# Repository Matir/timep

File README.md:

# Test Interface for Multiple Embedded Protocols

This is an Open Source Hardware board based around the FTDI FT2232H chip to
provide breakouts, buffering, and level conversion for a number of common
embedded hardware interfaces.  At present, this includes:

* SPI
* I2C
* JTAG
* SWD
* UART

It's intended to be easy to use and work with open source software, including
tools like OpenOCD and Flashrom.

## Archived

**This will not be maintained in any way. This eventually served as a prototype
and inspiration for [Tigard](https://github.com/tigard-tools/tigard), which was
productionized by [@securelyfitz](https://github.com/securelyfitz).**

## Usage

### Hardware Hookup

The hardware has dedicated headers for a variety of electrical interfaces.
Connect the desired interface to you target.  The pinout for SPI, I2C and UART
are printed on the board, SWD follows the ARM SWD standard, and JTAG is the ARM
20 pin JTAG interface.  (Electrically, however, it should work with most any
processor supporting JTAG.)

You may only use one of the SPI, I2C, SWD, and JTAG interfaces at any given
time.  The UART is handled by dedicated pins in the FT2232H, so can be used
simultaneously with one of the other interfaces.

There are 3 switches on the board.  The mode switch selects how the reference
power (for the interface) and the target are connected:

* **Isolated**: The interface is powered by the on-board voltage regulators, and the
  target must be powered by its own power supplies.  The power rails are not
  connected to one another.  You will almost always want to use this mode.
* **Bridged**: The interface is powered by the on-board voltage regulators which
  will also supply power to the target.  **The target must not be separately
  powered.**  This mode is useful for e.g., programming SPI/I2C flash out of
  circuit, or powering very small circuits -- maximum stable load is around 200mA.
* **Target**: The interface is partially powered from the target.
  (Specifically, the reference voltage for the level shifters.)  In theory, this
  can be used for cases where the target voltage is not 5v, 3.3v, or 1.8v.  The
  target voltage must still remain under 5V!

Note that the *ground* of your computer is connected to the *ground* of your
target when you connect with this.  In almost all cases, this is not a problem,
but if both are powered via the wall ("mains"), there is a risk of noise due to
ground loops, etc.

The voltage switch allows you to select the I/O voltage used in `Isolated` or
`Bridged` mode.  It does nothing (well, except change an LED) in `Target` mode.
5V is supplied directly from the USB input, and there are onboard regulators
for 3.3v and 1.8v.

The remaining switch selects between JTAG/SPI and I2C/SWD.  I2C and SWD use a
bidirectional data line, so require special handling.

### Software

I've tested the board with `OpenOCD` for JTAG/SWD use and `flashrom` for SPI/I2C
flash.  I'm planning to make a demo target board with a handful of interfaces on
it and provide that here in the future.

With `OpenOCD`, use the configuration file in `configs`.  You will also need a
target configuration.  Time permitting, I will post a tutorial on the use of
TIMEP and OpenOCD to debug targets.

With `flashrom`:

```
flashrom -p ft2232_spi:type=2232H,port=B,divisor=4
```

Use of `port=B` is critical, port `A` is wired to the UART, so will not work as
you intend.  :)

### Protections

Some efforts have been made to protect against mistakes that will destroy your
hardware, but there is still some risk in using this if connected improperly.

Included protection in current revision:

* Current limiting resistors on I/O lines.
* 5v+ tolerant I/O.
* Warnings in the README.  :)

Shorting power to ground may damage the target, the TIMEP interface, or the USB
port on your computer (if running in 5V mode).  This is unlikely, but be careful
with your connections.

Using the wrong voltage may damage components not rated for that voltage.  Any
voltage up to 5v is tolerated on the interface board I/O pins, but beyond that
may result in damage.

Additional protection that could be considered:

* Polyfuses on power/ground rails to computer.
* Clamping diodes on USB lines.
* Clamping diodes on I/O lines.

These have not been added because I have been trying to keep BOM cost down to
get these in the hands of as many hardware hackers as possible.

## License

Copyright 2020 Google, LLC

Maintainer: David Tomaschik <david@systemoverlord.com>

Please see [CONTRIBUTORS.md](CONTRIBUTORS.md) for credit to all contributors.

Licensed under the Apache License, Version 2.0 (the "License");
you may not use this file except in compliance with the License.
You may obtain a copy of the License at

    https://www.apache.org/licenses/LICENSE-2.0

Unless required by applicable law or agreed to in writing, software
distributed under the License is distributed on an "AS IS" BASIS,
WITHOUT WARRANTIES OR CONDITIONS OF ANY KIND, either express or implied.
See the License for the specific language governing permissions and
limitations under the License.

This is not an officially supported Google product.

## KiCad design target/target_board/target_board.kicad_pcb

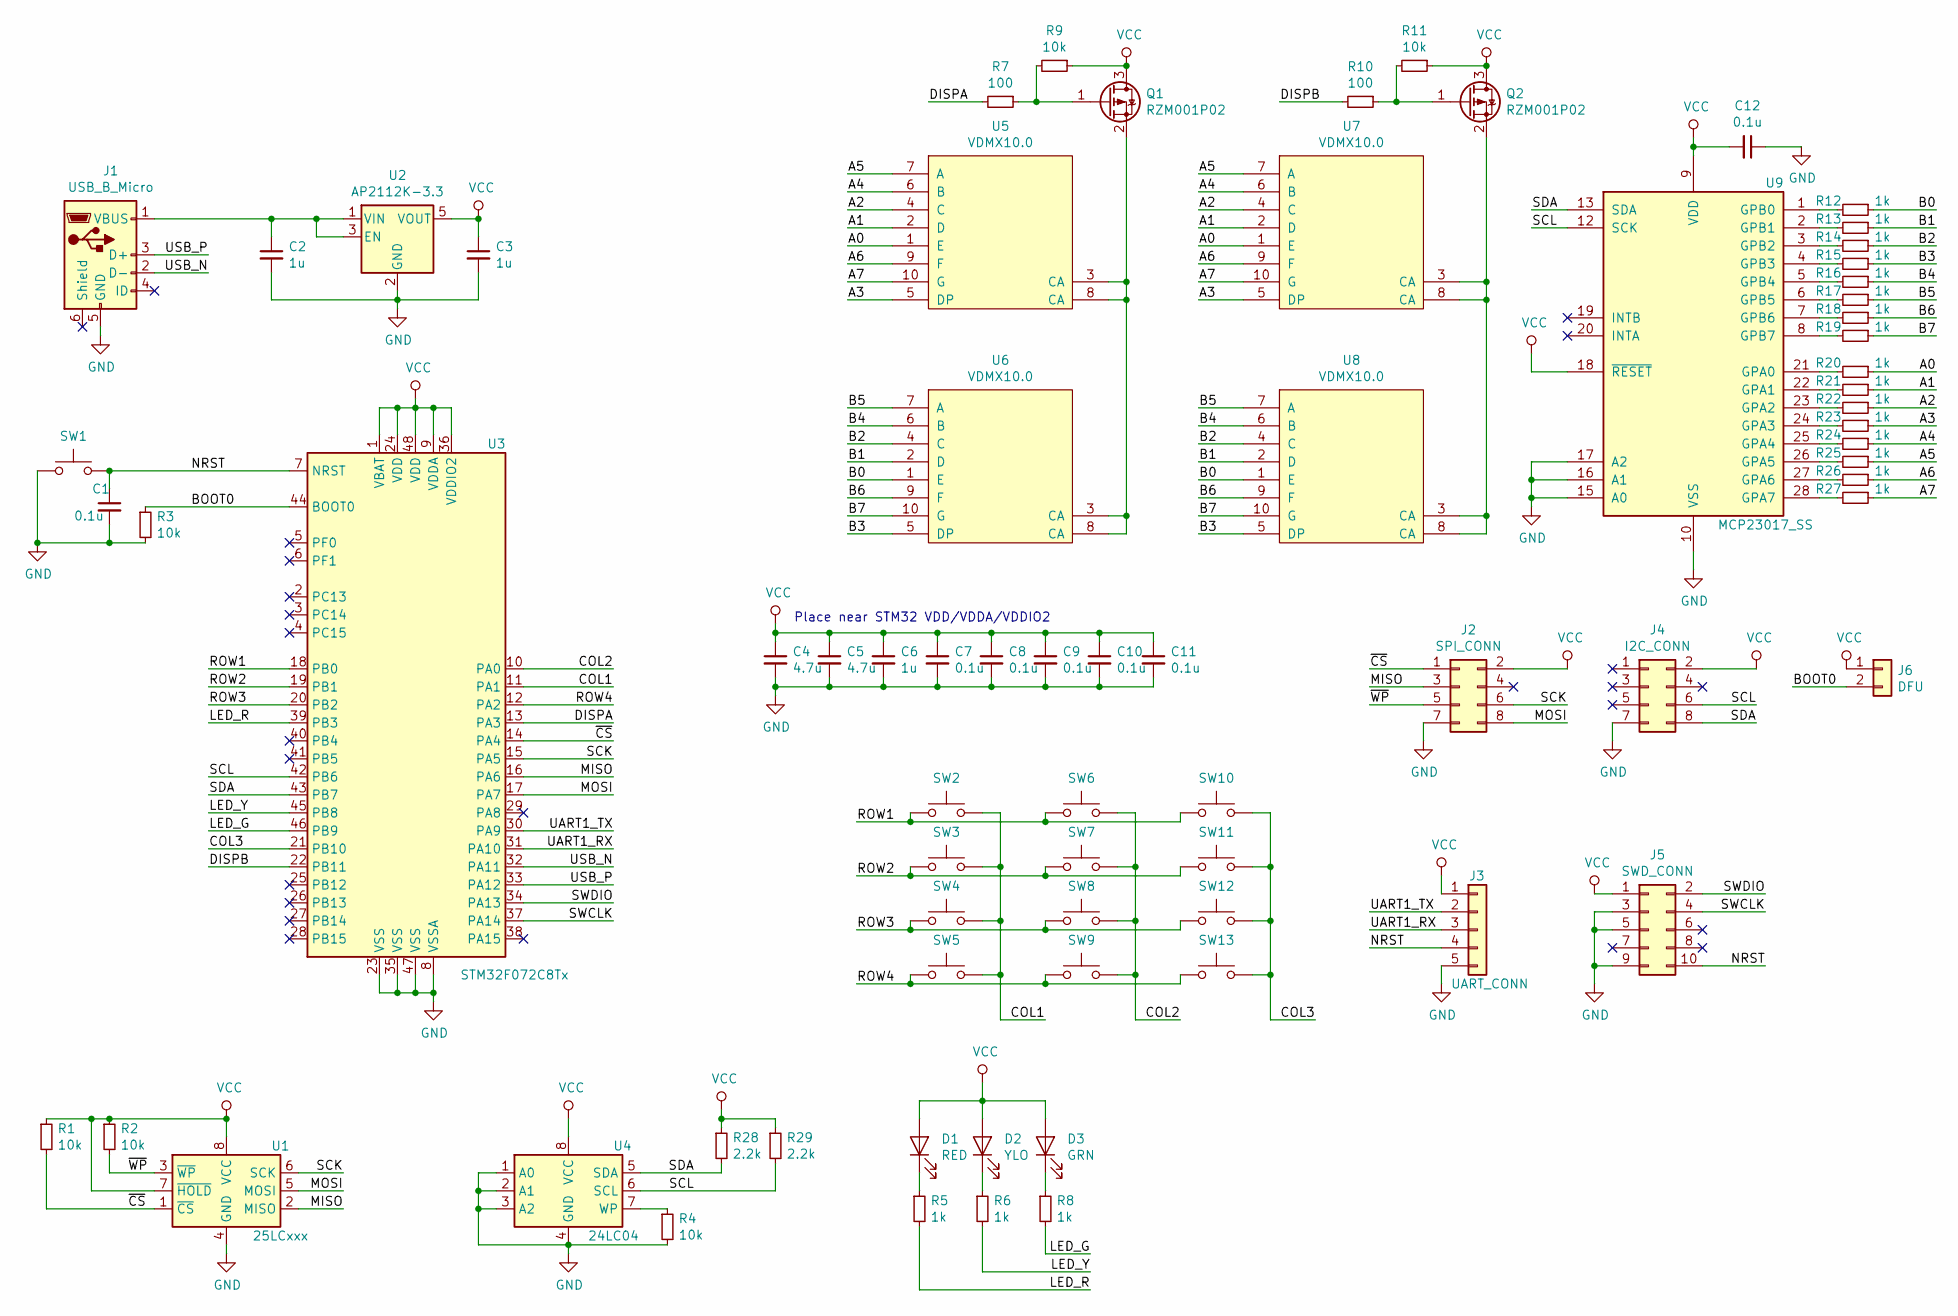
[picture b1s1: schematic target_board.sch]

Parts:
C1, C7, C8, C9, C10, C11, C12: 0.1u; C_0603_1608Metric
C2, C3, C6: 1u; C_0603_1608Metric
C4, C5: 4.7u; C_0603_1608Metric
D1: RED; LED_0603_1608Metric_Castellated
D2: YLO; LED_0603_1608Metric_Castellated
D3: GRN; LED_0603_1608Metric_Castellated
J1: USB_B_Micro; USB_Micro-B_Amphenol_10103594-0001LF_Horizontal
J2: SPI_CONN; PinHeader_2x04_P2.54mm_Vertical
J3: UART_CONN; PinHeader_1x05_P2.54mm_Vertical
J4: I2C_CONN; PinHeader_2x04_P2.54mm_Vertical
J5: SWD_CONN; PinHeader_2x05_P1.27mm_Vertical
J6: DFU; PinHeader_1x02_P2.54mm_Vertical
Q1, Q2: RZM001P02; SOT-723
R1, R2, R3, R4, R9, R11: 10k; R_0603_1608Metric
R5, R6, R8, R12, R13, R14, R15, R16, R17, R18, R19, R20, R21, R22, R23, R24, R25, R26, R27: 1k; R_0603_1608Metric
R7, R10: 100; R_0603_1608Metric
R28, R29: 2.2k; R_0603_1608Metric
SW1, SW2, SW3, SW4, SW5, SW6, SW7, SW8, SW9, SW10, SW11, SW12, SW13: SW_Push; SW_SPST_PTS645
U1: 25LCxxx; SOIC-8_3.9x4.9mm_P1.27mm
U2: AP2112K-3.3; SOT-23-5
U3: STM32F072C8Tx; LQFP-48_7x7mm_P0.5mm
U4: 24LC04; SOIC-8_3.9x4.9mm_P1.27mm
U5, U6, U7, U8: VDMX10.0
U9: MCP23017_SS; SSOP-28_5.3x10.2mm_P0.65mm

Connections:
/A0: R20.1, U5.1 (E), U7.1 (E)
/A1: R21.1, U5.2 (D), U7.2 (D)
/A2: R22.1, U5.4 (C), U7.4 (C)
/A3: R23.1, U5.5 (DP), U7.5 (DP)
/A4: R24.1, U5.6 (B), U7.6 (B)
/A5: R25.1, U5.7 (A), U7.7 (A)
/A6: R26.1, U5.9 (F), U7.9 (F)
/A7: R27.1, U5.10 (G), U7.10 (G)
/B0: R12.1, U6.1 (E), U8.1 (E)
/B1: R13.1, U6.2 (D), U8.2 (D)
/B2: R14.1, U6.4 (C), U8.4 (C)
/B3: R15.1, U6.5 (DP), U8.5 (DP)
/B4: R16.1, U6.6 (B), U8.6 (B)
/B5: R17.1, U6.7 (A), U8.7 (A)
/B6: R18.1, U6.9 (F), U8.9 (F)
/B7: R19.1, U6.10 (G), U8.10 (G)
/BOOT0: J6.2, R3.1, U3.44 (BOOT0)
/COL1: SW2.2, SW3.2, SW4.2, SW5.2, U3.11 (PA1)
/COL2: SW6.2, SW7.2, SW8.2, SW9.2, U3.10 (PA0)
/COL3: SW10.2, SW11.2, SW12.2, SW13.2, U3.21 (PB10)
/DISPA: R7.2, U3.13 (PA3)
/DISPB: R10.2, U3.22 (PB11)
/LED_G: R8.2, U3.46 (PB9)
/LED_R: R5.2, U3.39 (PB3)
/LED_Y: R6.2, U3.45 (PB8)
/MISO: J2.3, U1.2 (MISO), U3.16 (PA6)
/MOSI: J2.8, U1.5 (MOSI), U3.17 (PA7)
/NRST: C1.1, J3.4, J5.10, SW1.2, U3.7 (NRST)
/ROW1: SW2.1, SW6.1, SW10.1, U3.18 (PB0)
/ROW2: SW3.1, SW7.1, SW11.1, U3.19 (PB1)
/ROW3: SW4.1, SW8.1, SW12.1, U3.20 (PB2)
/ROW4: SW5.1, SW9.1, SW13.1, U3.12 (PA2)
/SCK: J2.6, U1.6 (SCK), U3.15 (PA5)
/SCL: J4.6, R29.2, U3.42 (PB6), U4.6 (SCL), U9.12 (SCK)
/SDA: J4.8, R28.2, U3.43 (PB7), U4.5 (SDA), U9.13 (SDA)
/SWCLK: J5.4, U3.37 (PA14)
/SWDIO: J5.2, U3.34 (PA13)
/UART1_RX: J3.3, U3.31 (PA10)
/UART1_TX: J3.2, U3.30 (PA9)
/USB_N: J1.2 (D-), U3.32 (PA11)
/USB_P: J1.3 (D+), U3.33 (PA12)
/~CS: J2.1, R1.2, U1.1 (~CS), U3.14 (PA4)
/~WP: J2.5, R2.2, U1.3 (~WP)
GND: C1.2, C2.2, C3.2, C4.2, C5.2, C6.2, C7.2, C8.2, C9.2, C10.2, C11.2, C12.1, J1.5 (GND), J2.7, J3.5, J4.7, J5.3, J5.5, J5.9, R3.2, R4.2, SW1.1, U1.4 (GND), U2.2 (GND), U3.8 (VSSA), U3.23 (VSS), U3.35 (VSS), U3.47 (VSS), U4.1 (A0), U4.2 (A1), U4.3 (A2), U4.4 (GND), U9.10 (VSS), U9.15 (A0), U9.16 (A1), U9.17 (A2)
unnamed: C2.1, J1.1 (VBUS), U2.1 (VIN), U2.3 (EN)
unnamed: D1.1 (K), R5.1
unnamed: D2.1 (K), R6.1
unnamed: D3.1 (K), R8.1
unnamed: Q1.1 (G), R7.1, R9.2
unnamed: Q1.2 (S), U5.3 (CA), U5.8 (CA), U6.3 (CA), U6.8 (CA)
unnamed: Q2.1 (G), R10.1, R11.2
unnamed: Q2.2 (S), U7.3 (CA), U7.8 (CA), U8.3 (CA), U8.8 (CA)
unnamed: R4.1, U4.7 (WP)
unnamed: R12.2, U9.1 (GPB0)
unnamed: R13.2, U9.2 (GPB1)
unnamed: R14.2, U9.3 (GPB2)
unnamed: R15.2, U9.4 (GPB3)
unnamed: R16.2, U9.5 (GPB4)
unnamed: R17.2, U9.6 (GPB5)
unnamed: R18.2, U9.7 (GPB6)
unnamed: R19.2, U9.8 (GPB7)
unnamed: R20.2, U9.21 (GPA0)
unnamed: R21.2, U9.22 (GPA1)
unnamed: R22.2, U9.23 (GPA2)
unnamed: R23.2, U9.24 (GPA3)
unnamed: R24.2, U9.25 (GPA4)
unnamed: R25.2, U9.26 (GPA5)
unnamed: R26.2, U9.27 (GPA6)
unnamed: R27.2, U9.28 (GPA7)
VCC: C3.1, C4.1, C5.1, C6.1, C7.1, C8.1, C9.1, C10.1, C11.1, C12.2, D1.2 (A), D2.2 (A), D3.2 (A), J2.2, J3.1, J4.2, J5.1, J6.1, Q1.3 (D), Q2.3 (D), R1.1, R2.1, R9.1, R11.1, R28.1, R29.1, U1.7 (~HOLD), U1.8 (VCC), U2.5 (VOUT), U3.1 (VBAT), U3.9 (VDDA), U3.24 (VDD), U3.36 (VDDIO2), U3.48 (VDD), U4.8 (VCC), U9.9 (VDD), U9.18 (~RESET~)

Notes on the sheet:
Place near STM32 VDD/VDDA/VDDIO2

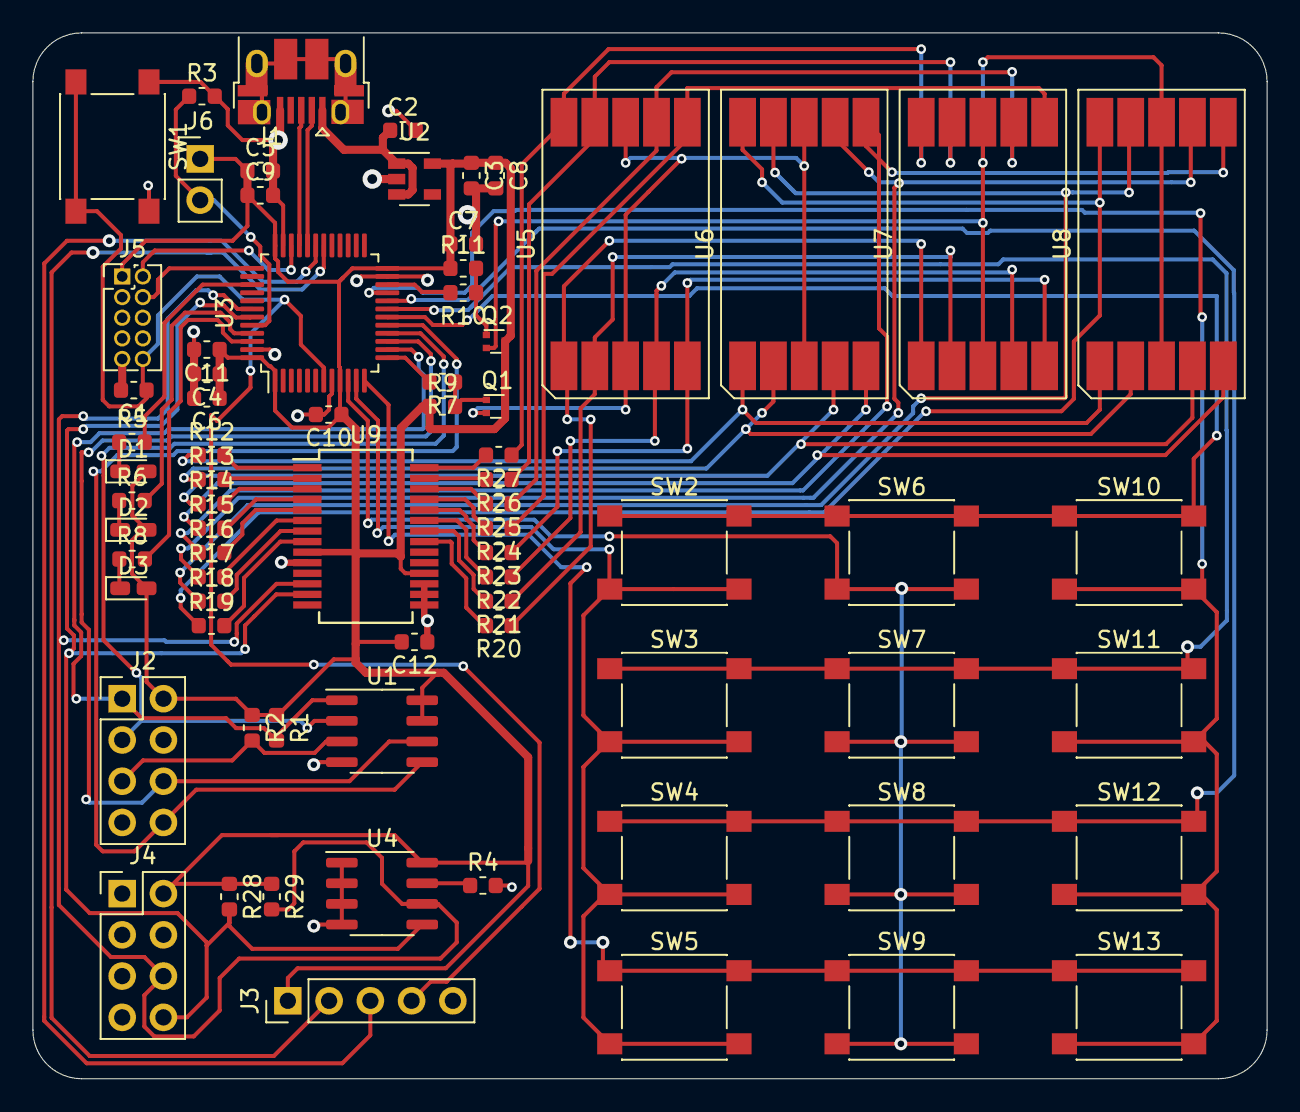
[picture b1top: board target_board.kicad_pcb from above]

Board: 2 copper layers, 76.0 x 64.4 mm, 74 parts (0 on the bottom side), 70 nets.

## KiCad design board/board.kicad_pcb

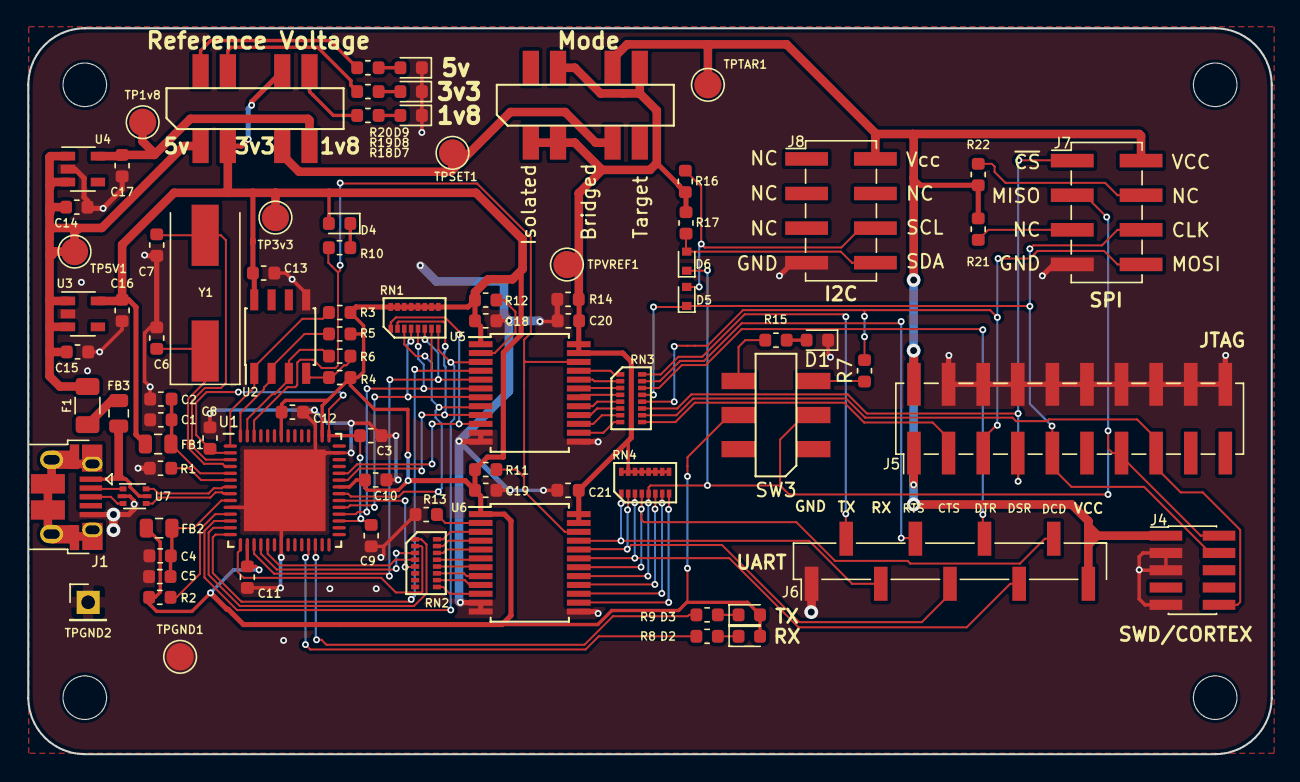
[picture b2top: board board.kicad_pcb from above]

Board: 2 copper layers, 91.3 x 53.3 mm, 89 parts (0 on the bottom side), 90 nets.

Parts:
C1, C4: 2.2u; C_0603_1608Metric
C2, C5, C8, C9, C10, C11, C12, C13, C18, C19, C20, C21: 0.1u; C_0603_1608Metric
C3, C14, C15, C16, C17: 3.3u; C_0603_1608Metric
C6, C7: 27pf; C_0603_1608Metric
D1, D2, D3, D4: LED; LED_0603_1608Metric
D5, D6: RB751S40; D_SOD-523
D7: 1v8; LED_0603_1608Metric
D8: 3v3; LED_0603_1608Metric
D9: 5v; LED_0603_1608Metric
F1: 500mA; Fuse_1206_3216Metric
FB1, FB2, FB3: 100; L_0805_2012Metric
H1, H2, H3, H4: MountingHole; MountingHole_3.2mm_M3
J1: USB_B_Micro; USB_Micro-B_Amphenol_10103594-0001LF_Horizontal
J4: SWD_CONN; PinHeader_2x05_P1.27mm_Vertical_SMD
J5: JTAG_CONN; PinHeader_2x10_P2.54mm_Vertical_SMD
J6: UART_Conn; PinHeader_1x09_P2.54mm_Vertical_SMD_Pin1Left
J7: SPI_CONN; PinHeader_2x04_P2.54mm_Vertical_SMD
J8: I2C_CONN; PinHeader_2x04_P2.54mm_Vertical_SMD
R1: 12k, 1%; R_0603_1608Metric
R2, R3, R4, R6, R11, R12, R13, R21, R22: 10k; R_0603_1608Metric
R5, R16, R17: 2.2k; R_0603_1608Metric
R7: 330; R_0603_1608Metric
R8, R9, R10, R15, R18, R19, R20: 1k; R_0603_1608Metric
R14: 1M; R_0603_1608Metric
RN1, RN4: 100k; EXB2HV
RN2, RN3: 100; EXB2HV
SW1, SW2: SW_DP3T; JS203011SCQN
SW3: SW_DPDT_x2; JS202011SCQN
TP1v8, TP3v3: TestPoint; TestPoint_Pad_D2.0mm
TP5V1: TP5V; TestPoint_Pad_D2.0mm
TPGND1: TestPoint; TestPoint_Pad_D2.0mm
TPGND2: TestPoint; PinHeader_1x01_P2.54mm_Vertical
TPSET1: TestPoint; TestPoint_Pad_D2.0mm
TPTAR1: TestPoint; TestPoint_Pad_D2.0mm
TPVREF1: TestPoint; TestPoint_Pad_D2.0mm
U1: FT2232H-56; FT2232H-56Q
U2: 93LC46B; SOIC-8_3.9x4.9mm_P1.27mm
U3: AP2112K-3.3; SOT-23-5
U4: AP2112K-1.8; SOT-23-5
U5, U6: SN74LVC8T245; SSOP-24_5.3x8.2mm_P0.65mm
U7: USBLC6; SOT-666
Y1: 12.000MHz; Crystal_SMD_HC49-SD

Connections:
+1V8: C17.1, SW1.4, TP1v8.1, U4.5
+3V3: C10.1, C11.1, C12.1, C13.1, C16.1, C18.1, C19.1, D2.2, D3.2, D4.2, FB1.1, FB2.1, R2.2, R3.1, R4.1, R6.1, R11.1, R12.2, RN1.9, RN1.10, RN1.11, RN1.12, RN1.13, RN1.14, RN1.15, RN1.16, SW1.2, SW1.7, SW3.5, TP3v3.1, U1.16, U1.36, U1.44, U1.50, U2.8, U3.5, U5.1, U6.1
+5V: C14.1, C15.1, F1.1, SW1.1, TP5V1.1, U3.1, U3.3, U4.1, U4.3
/AD0: RN1.8, U1.12, U5.3
/AD1: RN2.1, U1.13
/AD2: RN1.7, U1.14, U5.4
/AD3: RN2.2, U1.15
/AD4: RN1.6, U1.17, U5.5
/AD5: RN2.3, U1.18
/AD6: RN2.4, U1.19
/BD0: RN1.5, U1.32, U5.6
/BD1: RN1.4, U1.33, U5.7
/BD2: RN2.5, U1.34
/BD3: RN1.3, U1.35, U5.8
/BD4: RN1.2, U1.37, U5.9
/BD5: RN1.1, U1.38, U5.10
/CLK: D5.1, J4.4, J5.9, J7.6, RN3.13
/CS: J5.7, J7.1, RN3.11
/DI: D6.1, J4.2, J5.13, J7.3, RN4.5, SW3.2, U6.17
/DO: J5.5, J7.8, R7.2, RN3.12
/FT2232 Module/EECLK: R6.2, U1.56, U2.2
/FT2232 Module/EECS: R3.2, U1.1, U2.1
/FT2232 Module/EEDATA: R5.1, U1.55, U2.3
/FT2232 Module/OSCI: C7.1, U1.3, Y1.2
/FT2232 Module/OSCO: C6.1, U1.4, Y1.1
/FT2232 Module/VPHY: C1.1, C2.1, FB1.2, U1.5
/FT2232 Module/VPLL: C4.1, C5.1, FB2.2, U1.9
/FT2232 Module/VREG: C3.1, C8.1, C9.1, U1.2, U1.31, U1.43
/Power Regulators/Vset: SW1.3, SW2.3, TPSET1.1
/RXLED: R8.2, U1.25
/SCL: D5.2, J8.6, R16.2
/SDA: D6.2, J8.8, R17.2
/TXLED: R9.2, U1.26
/UART_RX: J6.3, RN4.1, U6.21
/UART_TX: J6.2, RN3.16
/USB_N: U1.7, U7.6
/USB_P: U1.8, U7.4
/VBUS: FB3.2, J1.1, U7.5
/VREF: C20.1, C21.1, R14.1, R16.1, R17.1, RN4.9, RN4.10, RN4.11, RN4.12, RN4.13, RN4.14, RN4.15, RN4.16, SW2.1, SW2.2, SW2.6, SW2.8, TPVREF1.1, U5.23, U5.24, U6.23, U6.24
/VTARGET: J4.1, J5.1, J5.2, J6.9, J7.2, J8.2, R21.2, R22.1, SW2.7, TPTAR1.1
/~ENABLE: R10.2, R11.2, U1.54, U5.22, U6.22
/~SRST: J4.10, J5.15, RN3.10
/~TRST: J5.3, RN3.9
/~UART_CTS: J6.5, RN4.2, U6.20
/~UART_DCD: J6.8, RN4.4, U6.18
/~UART_DSR: J6.7, RN4.3, U6.19
/~UART_DTR: J6.6, RN3.14
/~UART_RTS: J6.4, RN3.15
GND: C1.2, C2.2, C3.2, C4.2, C5.2, C6.2, C7.2, C8.2, C9.2, C10.2, C11.2, C12.2, C13.2, C14.2, C15.2, C16.2, C17.2, C18.2, C19.2, C20.2, C21.2, D1.1, D7.1, D8.1, D9.1, J1.5, J4.3, J4.5, J4.9, J5.4, J5.6, J5.8, J5.10, J5.12, J5.14, J5.16, J5.18, J5.20, J6.1, J7.7, J8.7, R1.2, R13.2, R14.2, TPGND1.1, TPGND2.1, U1.10, U1.21, U1.41, U1.45, U2.5, U3.2, U4.2, U5.11, U5.12, U5.13, U6.11, U6.12, U6.13, U7.2
unnamed: D1.2, R15.2
unnamed: D2.1, R8.1
unnamed: D3.1, R9.1
unnamed: D4.1, R10.1
unnamed: D7.2, R18.2
unnamed: D8.2, R19.2
unnamed: D9.2, R20.2
unnamed: F1.2, FB3.1
unnamed: J1.2, U7.1
unnamed: J1.3, U7.3
unnamed: J7.4, R22.2
unnamed: J7.5, R21.1
unnamed: R1.1, U1.6
unnamed: R2.1, U1.11
unnamed: R4.2, R5.2, U2.4
unnamed: R7.1, SW3.3
unnamed: R12.1, U5.2
unnamed: R13.1, U6.2
unnamed: R15.1, SW3.6
unnamed: R18.1, SW1.8
unnamed: R19.1, SW1.6
unnamed: R20.1, SW1.5
unnamed: RN2.9, U6.10
unnamed: RN2.10, U6.9
unnamed: RN2.11, U6.8
unnamed: RN2.12, U6.7
unnamed: RN2.13, U6.6
unnamed: RN2.14, U6.5
unnamed: RN2.15, U6.4
unnamed: RN2.16, U6.3
unnamed: RN3.1, U5.21
unnamed: RN3.2, U5.20
unnamed: RN3.3, U5.19
unnamed: RN3.4, U5.18
unnamed: RN3.5, U5.17
unnamed: RN3.6, U5.16
unnamed: RN3.7, U5.15
unnamed: RN3.8, U5.14
unnamed: RN4.6, U6.16
unnamed: RN4.7, U6.15
unnamed: RN4.8, U6.14

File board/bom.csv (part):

Reference, Value, Footprint, Datasheet, Digikey, P/N, Comment
"J1","USB_B_Micro","Connector_USB:USB_Micro-B_Amphenol_10103594-0001LF_Horizontal","~","609-4050-1-ND","10103594",""
"FB3","100","Inductor_SMD:L_0805_2012Metric","~","445-1567-1-ND","MPZ2012S101AT000",""
"D2","LED","LED_SMD:LED_0603_1608Metric","~","732-4979-1-ND","150060SS75000","Substitution Okay"
"D3","LED","LED_SMD:LED_0603_1608Metric","~","732-4979-1-ND","150060SS75000","Substitution Okay"
"R8","1k","Resistor_SMD:R_0603_1608Metric","~","RMCF0603JT1K00CT-ND","RMCF0603JT1K00","Substitution Okay"
"R9","1k","Resistor_SMD:R_0603_1608Metric","~","RMCF0603JT1K00CT-ND","RMCF0603JT1K00","Substitution Okay"
"D4","LED","LED_SMD:LED_0603_1608Metric","~","732-4979-1-ND","150060SS75000","Substitution Okay"
"R10","1k","Resistor_SMD:R_0603_1608Metric","~","RMCF0603JT1K00CT-ND","RMCF0603JT1K00","Substitution Okay"
"U5","SN74LVC8T245","Package_SO:SSOP-24_5.3x8.2mm_P0.65mm","","296-21065-1-ND","SN74LVC8T245DBR",""
"U6","SN74LVC8T245","Package_SO:SSOP-24_5.3x8.2mm_P0.65mm","","296-21065-1-ND","SN74LVC8T245DBR",""
"R11","10k","Resistor_SMD:R_0603_1608Metric","~","RMCF0603JT10K0CT-ND","RMCF0603JT10K0","Substitution Okay"
"C18","0.1u","Capacitor_SMD:C_0603_1608Metric","~","1276-1857-1-ND","CL10A104KA8NNNC","Substitution Okay"
"C19","0.1u","Capacitor_SMD:C_0603_1608Metric","~","1276-1857-1-ND","CL10A104KA8NNNC","Substitution Okay"
"C20","0.1u","Capacitor_SMD:C_0603_1608Metric","~","1276-1857-1-ND","CL10A104KA8NNNC","Substitution Okay"
"C21","0.1u","Capacitor_SMD:C_0603_1608Metric","~","1276-1857-1-ND","CL10A104KA8NNNC","Substitution Okay"
"R12","10k","Resistor_SMD:R_0603_1608Metric","~","RMCF0603JT10K0CT-ND","RMCF0603JT10K0","Substitution Okay"
"R13","10k","Resistor_SMD:R_0603_1608Metric","~","RMCF0603JT10K0CT-ND","RMCF0603JT10K0","Substitution Okay"
"R14","1M","Resistor_SMD:R_0603_1608Metric","~","RMCF0603JT1M00CT-ND","RMCF0603JT1M00","Substitution Okay"
"RN1","100k","Matir_Parts:EXB2HV","~","Y1104CT-ND","EXB-2HV104JV",""
"RN2","100","Matir_Parts:EXB2HV","~","Y1331CT-ND","EXB-2HV331JV",""
"RN4","100k","Matir_Parts:EXB2HV","~","Y1104CT-ND","EXB-2HV104JV",""
"RN3","100","Matir_Parts:EXB2HV","~","Y1331CT-ND","EXB-2HV331JV",""
"J6","UART_Conn","Connector_PinHeader_2.54mm:PinHeader_1x09_P2.54mm_Vertical_SMD_Pin1Left","~","TSM-109-01-L-SV-P-ND","TSM-109-01-L-SV-P",""
"J5","JTAG_CONN","Connector_PinHeader_2.54mm:PinHeader_2x10_P2.54mm_Vertical_SMD","~","609-6477-1-ND","95278-801A20LF",""
"J4","SWD_CONN","Connector_PinHeader_1.27mm:PinHeader_2x05_P1.27mm_Vertical_SMD","~","609-6118-1-ND","20021121-00010C1L",""
"J7","SPI_CONN","Connector_PinHeader_2.54mm:PinHeader_2x04_P2.54mm_Vertical_SMD","~","609-5811-1-ND","95278-101A08LF",""
"J8","I2C_CONN","Connector_PinHeader_2.54mm:PinHeader_2x04_P2.54mm_Vertical_SMD","~","609-5811-1-ND","95278-101A08LF",""
"R16","2.2k","Resistor_SMD:R_0603_1608Metric","~","RMCF0603JT2K20CT-ND","RMCF0603JT2K20","Substitution Okay"
"R17","2.2k","Resistor_SMD:R_0603_1608Metric","~","RMCF0603JT2K20CT-ND","RMCF0603JT2K20","Substitution Okay"
"D5","RB751S40","Diode_SMD:D_SOD-523","~","RB751S40T1GOSCT-ND","RB751S40T1G",""
"D6","RB751S40","Diode_SMD:D_SOD-523","~","RB751S40T1GOSCT-ND","RB751S40T1G",""
"H4","MountingHole","MountingHole:MountingHole_3.2mm_M3","~"
"H2","MountingHole","MountingHole:MountingHole_3.2mm_M3","~"
"H1","MountingHole","MountingHole:MountingHole_3.2mm_M3","~"
"H3","MountingHole","MountingHole:MountingHole_3.2mm_M3","~"
"SW3","SW_DPDT_x2","Matir_Parts:JS202011SCQN","","401-2002-1-ND","JS202011SCQN",""
"R7","330","Resistor_SMD:R_0603_1608Metric","~","RMCF0603JT330RCT-ND","RMCF0603JT330R","Substitution Okay"
"R15","1k","Resistor_SMD:R_0603_1608Metric","~","RMCF0603JT1K00CT-ND","RMCF0603JT1K00","Substitution Okay"
"D1","LED","LED_SMD:LED_0603_1608Metric","~","732-4979-1-ND","150060SS75000","Substitution Okay"
"R22","10k","Resistor_SMD:R_0603_1608Metric","~","RMCF0603JT10K0CT-ND","RMCF0603JT10K0","Substitution Okay"
"R21","10k","Resistor_SMD:R_0603_1608Metric","~","RMCF0603JT10K0CT-ND","RMCF0603JT10K0","Substitution Okay"
"F1","500mA","Fuse:Fuse_1206_3216Metric","~","NANOSMDC050F/13.2-2CT-ND","NANOSMDC050F/13.2-2",""
"U7","USBLC6","Package_TO_SOT_SMD:SOT-666","","497-5026-1-ND","USBLC6-2P6",""
"U1","FT2232H-56","Matir_Parts:FT2232H-56Q","","768-1276-ND","FT2232H-56Q-TRAY",""
"C3","3.3u","Capacitor_SMD:C_0603_1608Metric","~","1276-1892-1-ND","CL10A335KP8NNNC","Substitution Okay"
"R1","12k, 1%","Resistor_SMD:R_0603_1608Metric","~","RMCF0603FT12K0CT-ND","RMCF0603FT12K0",""
"FB2","100","Inductor_SMD:L_0805_2012Metric","~","445-1567-1-ND","MPZ2012S101AT000",""
"FB1","100","Inductor_SMD:L_0805_2012Metric","~","445-1567-1-ND","MPZ2012S101AT000",""
"C4","2.2u","Capacitor_SMD:C_0603_1608Metric","~","1276-1183-1-ND","CL10A225KQ8NNNC","Substitution Okay"
"C2","0.1u","Capacitor_SMD:C_0603_1608Metric","~","1276-1857-1-ND","CL10A104KA8NNNC","Substitution Okay"
"C5","0.1u","Capacitor_SMD:C_0603_1608Metric","~","1276-1857-1-ND","CL10A104KA8NNNC","Substitution Okay"
"C1","2.2u","Capacitor_SMD:C_0603_1608Metric","~","1276-1183-1-ND","CL10A225KQ8NNNC","Substitution Okay"
"C8","0.1u","Capacitor_SMD:C_0603_1608Metric","~","1276-1857-1-ND","CL10A104KA8NNNC","Substitution Okay"
"C9","0.1u","Capacitor_SMD:C_0603_1608Metric","~","1276-1857-1-ND","CL10A104KA8NNNC","Substitution Okay"
"C10","0.1u","Capacitor_SMD:C_0603_1608Metric","~","1276-1857-1-ND","CL10A104KA8NNNC","Substitution Okay"
"C11","0.1u","Capacitor_SMD:C_0603_1608Metric","~","1276-1857-1-ND","CL10A104KA8NNNC","Substitution Okay"
"C12","0.1u","Capacitor_SMD:C_0603_1608Metric","~","1276-1857-1-ND","CL10A104KA8NNNC","Substitution Okay"
"R2","10k","Resistor_SMD:R_0603_1608Metric","~","RMCF0603JT10K0CT-ND","RMCF0603JT10K0","Substitution Okay"
"Y1","12.000MHz","Crystal:Crystal_SMD_HC49-SD","~","535-15006-1-ND","ABLS-12.000MHZ-20-B-3-H-T",""
"C7","27pf","Capacitor_SMD:C_0603_1608Metric","~","311-1063-1-ND","CC0603JRNPO9BN270",""
"C6","27pf","Capacitor_SMD:C_0603_1608Metric","~","311-1063-1-ND","CC0603JRNPO9BN270",""
"U2","93LC46B","Package_SO:SOIC-8_3.9x4.9mm_P1.27mm","http://ww1.microchip.com/downloads/en/DeviceDoc/20001749K.pdf","93LC46BT-I/SNCT-ND","93LC46BT-I/SN",""
"C13","0.1u","Capacitor_SMD:C_0603_1608Metric","~","1276-1857-1-ND","CL10A104KA8NNNC","Substitution Okay"
"R4","10k","Resistor_SMD:R_0603_1608Metric","~","RMCF0603JT10K0CT-ND","RMCF0603JT10K0","Substitution Okay"
"R6","10k","Resistor_SMD:R_0603_1608Metric","~","RMCF0603JT10K0CT-ND","RMCF0603JT10K0","Substitution Okay"
"R3","10k","Resistor_SMD:R_0603_1608Metric","~","RMCF0603JT10K0CT-ND","RMCF0603JT10K0","Substitution Okay"
"R5","2.2k","Resistor_SMD:R_0603_1608Metric","~","RMCF0603JT2K20CT-ND","RMCF0603JT2K20","Substitution Okay"
"C16","3.3u","Capacitor_SMD:C_0603_1608Metric","~","1276-1892-1-ND","CL10A335KP8NNNC","Substitution Okay"
"C14","3.3u","Capacitor_SMD:C_0603_1608Metric","~","1276-1892-1-ND","CL10A335KP8NNNC","Substitution Okay"
"C15","3.3u","Capacitor_SMD:C_0603_1608Metric","~","1276-1892-1-ND","CL10A335KP8NNNC","Substitution Okay"
"C17","3.3u","Capacitor_SMD:C_0603_1608Metric","~","1276-1892-1-ND","CL10A335KP8NNNC","Substitution Okay"
"U3","AP2112K-3.3","Package_TO_SOT_SMD:SOT-23-5","https://www.diodes.com/assets/Datasheets/AP2112.pdf","AP2112K-3.3TRG1DICT-ND","AP2112K-3.3TRG1",""
"U4","AP2112K-1.8","Package_TO_SOT_SMD:SOT-23-5","https://www.diodes.com/assets/Datasheets/AP2112.pdf","AP2112K-1.8TRG1DICT-ND","AP2112K-1.8TRG1",""
"SW1","SW_DP3T","Matir_Parts:JS203011SCQN","","CKN10849CT-ND","JS203011SCQN",""
"R18","1k","Resistor_SMD:R_0603_1608Metric","~","RMCF0603JT1K00CT-ND","RMCF0603JT1K00","Substitution Okay"
"R19","1k","Resistor_SMD:R_0603_1608Metric","~","RMCF0603JT1K00CT-ND","RMCF0603JT1K00","Substitution Okay"
"R20","1k","Resistor_SMD:R_0603_1608Metric","~","RMCF0603JT1K00CT-ND","RMCF0603JT1K00","Substitution Okay"
"D7","1v8","LED_SMD:LED_0603_1608Metric","~","732-4979-1-ND","150060SS75000","Substitution Okay"
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
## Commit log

2020-04-08 Prepare TIMEP for release.
2020-04-08 Update disclaimer.
2020-05-09 Update for release.
2020-05-10 Add protection (ESD, PTC fusing) to MicroUSB port
    Schematic changes:
    * No connect SHIELD on the MicroUSB port. Since we have no SHIELD GND, I
    think it's best to leave the shield unconnected rather than connect it
    to our digital GND and potentially introduce noise. This seems to be
    backed up by the FTDI USB Design Guidelines
    (https://www.ftdichip.com/Support/Documents/AppNotes/AN_146_USB_Hardware_Design_Guidelines_for_FTDI_ICs.pdf)
2020-05-10 Add CONTRIBUTORS file.
2020-05-11 Start work on a target board.
2020-05-12 Rough layout of components for target.
2020-05-12 Continue layout
2020-05-12 Route busses.
2020-05-12 Route most display
2020-05-12 Few airwires left.
2020-05-13 Finish routing.
2020-05-13 Make board smaller.
2020-05-13 Ignore .zip
2020-05-14 Add missing I2C pullups
2026-04-09 Add archived notice to README
    Added archived section indicating the project will not be maintained.

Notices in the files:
board/board.kicad_pcb:
(C) 2020 Google LLC
